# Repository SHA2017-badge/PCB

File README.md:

# PCB
This repository hosts the board files for the SHA2017 badge. There are a couple different revisions:
* _rev0_0_1_: First dev board
* _rev0_0_2_: First dev board with fixed IO error (not produced)
* _rev0_1_0_: "Pre-badge"
* _rev1_0_0_: Semi-final badge design - via under D3 shorts VCC to GND (oops)
* _rev1_0_1_: FINAL Badge design with short fixed and silkscreen art

The badge is designed in Eagle version 6.6.

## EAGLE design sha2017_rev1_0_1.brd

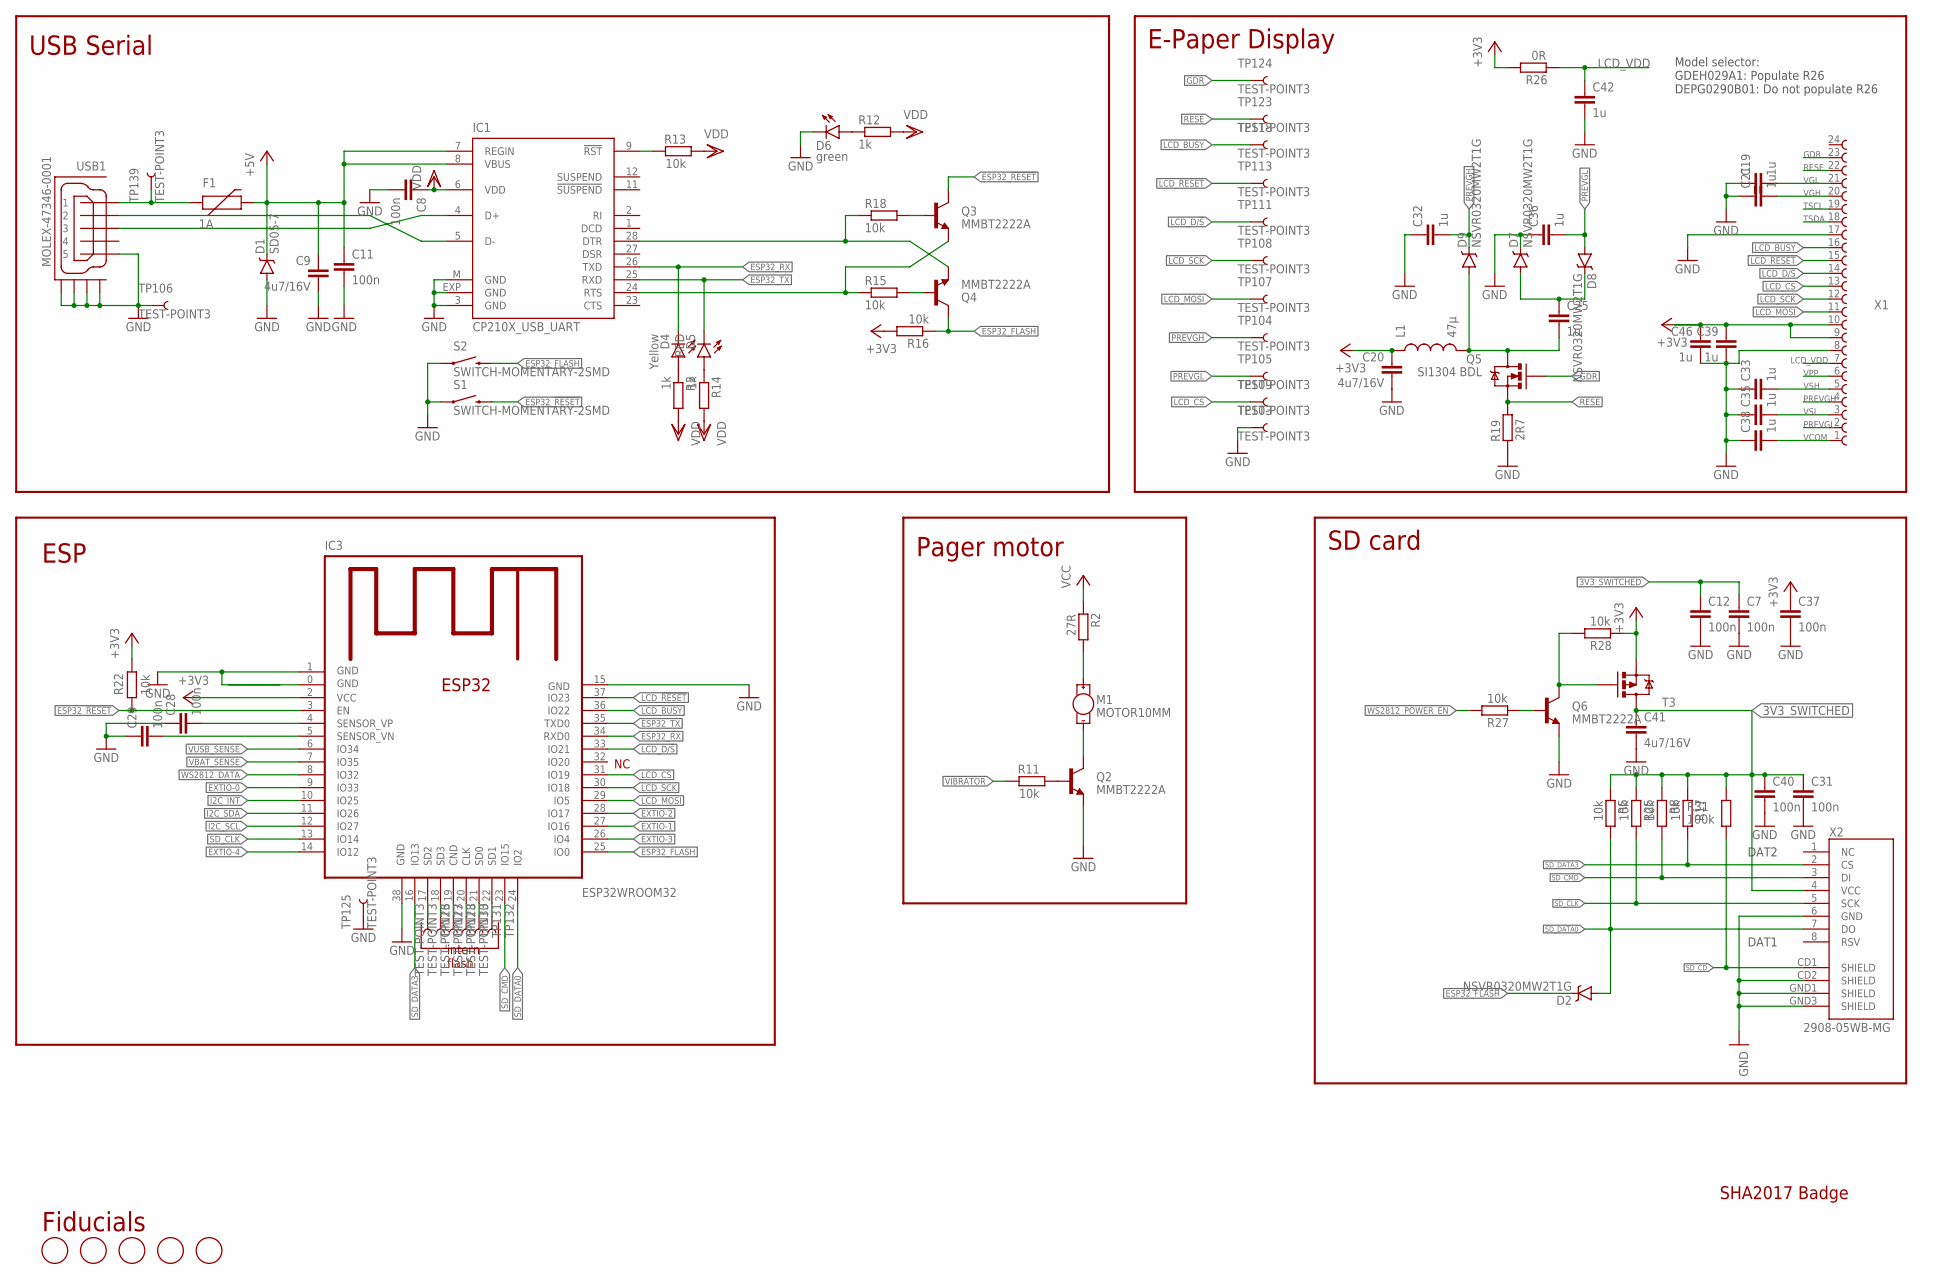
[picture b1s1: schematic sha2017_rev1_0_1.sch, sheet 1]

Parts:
C7, C8, C11, C12, C28, C29, C31, C37, C40: 100n; C0603-DASHES; PARTNO GRM188R71H104KA93D
C9, C20, C41: 4u7/16V; C0805; PARTNO GRM21BR61C475KA88K
C19, C21, C25, C32, C33, C35, C36, C38, C39, C42, C46: 1u; C0603-DASHES; PARTNO GRM188R61E105KA12D
D1: SD05-7; SOD-323; PARTNO SD05-7
D2, D7, D8, D9: NSVR0320MW2T1G; SOD-323; PARTNO BAT20JFILM
D4: Yellow; LED-0603
D5: RED; LED-0603
D6: green; LED-0603
F1: 1A; PTC-1206
FD1, FD2, FD3, FD4, FD5: FIDUCIAL; FIDUCIAL_1MM; PARTNO NAP
IC1: CP210X_USB_UART; MLP28; PARTNO CP2102-GMR
IC3: ESP32WROOM32; ESP32MOD
L1: 47µ; 1210; PARTNO NLCV32T-220K-EF
M1: MOTOR10MM; VIBE-MOTOR-10MM
Q2, Q3, Q4, Q6: MMBT2222A; SOT23-3; PARTNO BC817-25,215
Q5: SI1304 BDL; SOT323; PARTNO SI1308EDL-T1-GE3
R2: 27R; R1206; PARTNO ERJ-3GEYJ220V
R3, R12, R14: 1k; R0603-DASHES; PARTNO ERJ-3GEYJ102V
R5, R8, R11, R13, R15, R16, R17, R18, R22, R25, R27, R28: 10k; R0603-DASHES; PARTNO ERJ-3GEYJ103V
R19: 2R7; R0603-DASHES; PARTNO ERJ-3GEYJ5R1V
R26: 0R; R0603-DASHES; PARTNO ERJ-3GEYJ5R1V
R31: 100k; R0603-DASHES; PARTNO ERJ-3GEYJ104V
S1, S2: SWITCH-MOMENTARY-2SMD; TACTILE-SWITCH-SMD; PARTNO SKQGABE010
T3: MOSFET-PCHANNEL; SOT23-3
TP103, TP104, TP105, TP106, TP107, TP108, TP109, TP111, TP113, TP118, TP123, TP124, TP125, TP126, TP127, TP128, TP130, TP131, TP132, TP139: TEST-POINT3; PAD.03X.03; PARTNO NAP
USB1: MOLEX-47346-0001; MOLEX-47364-0001; PARTNO 10118192-0001LF
X1: 68712414022; PARTNO 68712414022
X2: 2908-05WB-MG; MICRO-SD-SOCKET-PP; PARTNO 2908-05WB-MG

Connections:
3V3_SWITCHED: C7.1, C12.1, C31.1, C40.1, C41.1, R5.2, R8.2, R17.2, R25.2, R31.1, T3.3 (D), X2.4 (VCC); also elsewhere on the board
+3V3: C20.1, C37.1, C39.1, C46.1, IC3.2 (VCC), L1.1, R16.2, R22.1, R26.1, R28.2, T3.2 (S), X1.9, X1.10; also elsewhere on the board
+5V: C9.1, C11.1, D1.C, F1.2, IC1.7 (REGIN), IC1.8 (VBUS); also elsewhere on the board
CD0: IC3.21 (SD0), TP131.P$1
CLK: IC3.20 (CLK), TP130.P$1
CND: IC3.19 (CND), TP128.P$1
ESP32_!RESET: IC3.3 (EN), Q3.3 (C), R22.2, S1.3 (2); also elsewhere on the board
ESP32_FLASH: D2.C, IC3.25 (IO0), Q4.3 (C), R16.1, S2.3 (2); also elsewhere on the board
ESP32_RX: D4.C, IC1.26 (TXD), IC3.34 (RXD0); also elsewhere on the board
ESP32_TX: D5.C, IC1.25 (RXD), IC3.35 (TXD0); also elsewhere on the board
EXTIO-0: IC3.9 (IO33); also elsewhere on the board
EXTIO-1: IC3.27 (IO16); also elsewhere on the board
EXTIO-2: IC3.28 (IO17); also elsewhere on the board
EXTIO-3: IC3.26 (IO4); also elsewhere on the board
EXTIO-4: IC3.14 (IO12); also elsewhere on the board
GDR: Q5.1 (G), TP124.P$1, X1.23
GND: C7.2, C8.2, C9.2, C11.2, C12.2, C19.1, C20.2, C21.1, C28.1, C29.1, C31.2, C32.1, C33.1, C35.1, C36.1, C37.2, C38.1, C39.2, C40.2, C41.2, C42.2, C46.2, D1.A, D6.C, D7.C, IC1.3 (GND), IC1.EXP (GND), IC1.M (GND), IC3.0 (GND), IC3.1 (GND), IC3.15 (GND), IC3.38 (GND), Q2.2 (E), Q6.2 (E), R19.2, S1.1, S2.1, TP103.P$1, TP106.P$1, TP125.P$1, USB1.5, USB1.GND1, USB1.GND2, USB1.GND3, USB1.GND4, X1.8, X1.17, X2.6 (GND), X2.CD2 (SHIELD), X2.GND1 (SHIELD), X2.GND3 (SHIELD); also elsewhere on the board
I2C_INT: IC3.10 (IO25); also elsewhere on the board
I2C_SCL: IC3.12 (IO27); also elsewhere on the board
I2C_SDA: IC3.11 (IO26); also elsewhere on the board
LCD_!RESET: IC3.37 (IO23), TP113.P$1, X1.15
LCD_BUSY: IC3.36 (IO22), TP118.P$1, X1.16
LCD_CS: IC3.31 (IO19), TP109.P$1, X1.13
LCD_D/!S: IC3.33 (IO21), TP111.P$1, X1.14
LCD_MOSI: IC3.29 (IO5), TP107.P$1, X1.11
LCD_SCK: IC3.30 (IO18), TP108.P$1, X1.12
LCD_VDD: C42.1, R26.2, X1.7
unnamed: IC1.9 (!RST), R13.2
unnamed: IC1.24 (RTS), Q3.2 (E), R15.1
unnamed: IC1.28 (DTR), Q4.2 (E), R18.1
unnamed: Q4.1 (B), R15.2
unnamed: Q3.1 (B), R18.2
unnamed: Q6.1 (B), R27.2
unnamed: M1.-, Q2.3 (C)
unnamed: Q6.3 (C), R28.1, T3.1 (G)
unnamed: M1.+, R2.1
unnamed: C25.1, D7.A, D8.C
unnamed: C25.2, D9.A, L1.2, Q5.3 (D)
unnamed: D6.A, R12.1
unnamed: D4.A, R3.1
unnamed: D5.A, R14.1
unnamed: F1.1, TP139.P$1, USB1.1
unnamed: C28.2, IC3.4 (SENSOR_VP)
unnamed: C29.2, IC3.5 (SENSOR_VN)
unnamed: Q2.1 (B), R11.1
PREVGH: C32.2, D9.C, TP104.P$1, X1.4
PREVGL: C36.2, D8.A, TP105.P$1, X1.2
RESE: Q5.2 (S), R19.1, TP123.P$1, X1.22
SD1: IC3.22 (SD1), TP132.P$1
SD2: IC3.17 (SD2), TP126.P$1
SD3: IC3.18 (SD3), TP127.P$1
SD_CD: R31.2, X2.CD1 (SHIELD); also elsewhere on the board
SD_CLK: IC3.13 (IO14), R25.1, X2.5 (SCK)
SD_CMD: IC3.23 (IO15), R8.1, X2.3 (DI)
SD_DATA0: D2.A, IC3.24 (IO2), R5.1, X2.7 (DO)
SD_DATA3: IC3.16 (IO13), R17.1, X2.2 (CS)
TSCL: X1.19
TSDA: X1.18
USB_DN_CON: IC1.5 (D-), USB1.2; also elsewhere on the board
USB_DP_CON: IC1.4 (D+), USB1.3; also elsewhere on the board
VBAT_SENSE: IC3.7 (IO35); also elsewhere on the board
VCC: R2.2; also elsewhere on the board
VCOM: C38.2, X1.1
VDD: C8.1, IC1.6 (VDD), R3.2, R12.2, R13.1, R14.2
VGH: C21.2, X1.20
VGL: C19.2, X1.21
VIBRATOR: R11.2; also elsewhere on the board
VPP: X1.6
VSH: C33.2, X1.5
VSL: C35.2, X1.3
VUSB_SENSE: IC3.6 (IO34); also elsewhere on the board
WS2812_DATA: IC3.8 (IO32); also elsewhere on the board
WS2812_POWER_EN: R27.1; also elsewhere on the board

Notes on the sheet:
USB Serial
E-Paper Display
SD card
intern flash
ESP
Fiducials
Pager motor
DAT1
DAT2
Model selector: GDEH029A1: Populate R26 DEPG0290B01: Do not populate R26
SHA2017 Badge

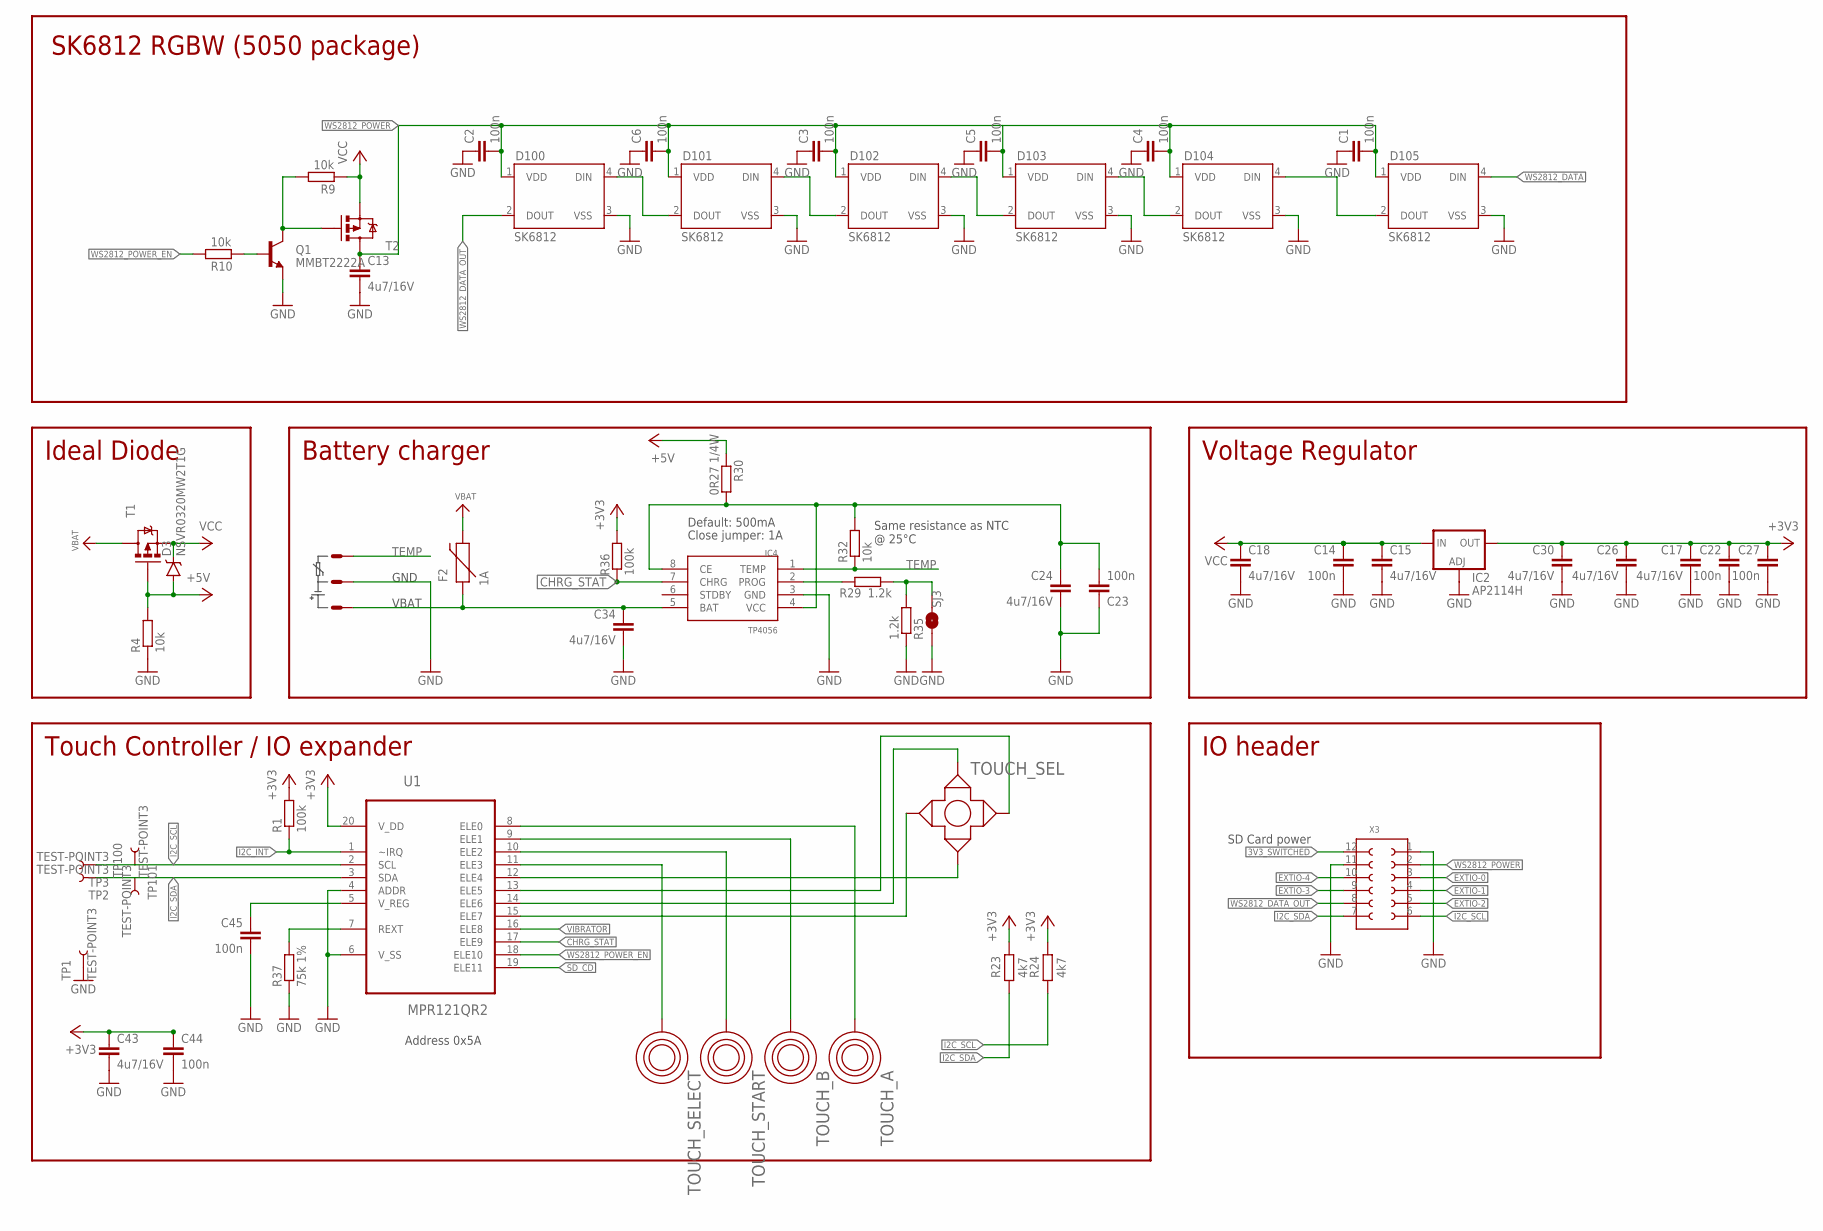
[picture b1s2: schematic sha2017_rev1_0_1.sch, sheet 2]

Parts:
C1, C2, C3, C4, C5, C6, C14, C22, C23, C27, C44, C45: 100n; C0603-DASHES; PARTNO GRM188R71H104KA93D
C13, C15, C17, C18, C24, C26, C30, C34, C43: 4u7/16V; C0805; PARTNO GRM21BR61C475KA88K
D3: NSVR0320MW2T1G; SOD-323; PARTNO BAT20JFILM
D100, D101, D102, D103, D104, D105: SK6812; WS2812B; PARTNO SK6812
F2: 1A; PTC-1206
IC2: AP2114H; SOT223; PARTNO AP7215-33YG-13
IC4: TP4056; SOP-8
Q1: MMBT2222A; SOT23-3; PARTNO BC817-25,215
R1, R36: 100k; R0603-DASHES; PARTNO ERJ-3GEYJ104V
R4, R9, R10: 10k; R0603-DASHES; PARTNO ERJ-3GEYJ103V
R23, R24: 4k7; R0603-DASHES; PARTNO ERJ-3GEYJ103V
R29, R35: 1.2k; R0603-DASHES; PARTNO ERJ-3GEYJ222V
R30: 0R27 1/4W; R1206; PARTNO ERJ-3GEYJ154V
R32: 10k; R0603-DASHES; PARTNO ERJ-3GEYJ154V
R37: 75k 1%; R0603-DASHES; PARTNO ERJ-3GEYJ104V
SJ3: JUMPER-PAD-2-NOYES_SILK; PAD-JUMPER-2-NO_YES_SILK; PARTNO NAP
T1, T2: MOSFET-PCHANNEL; SOT23-3
TOUCH_A: TOUCHROUND; TOUCH_BUTTON; PARTNO NAP
TOUCH_B: TOUCHROUND; TOUCH_BUTTON; PARTNO NAP
TOUCH_SEL: TOUCH_CROSS; PARTNO NAP
TOUCH_SELECT: TOUCHSELECT; TOUCH_SELECT
TOUCH_START: TOUCHSELECT; TOUCH_SELECT
TP1, TP2, TP3, TP100, TP101: TEST-POINT3; PAD.03X.03; PARTNO NAP
U1: MPR121QR2; QFN40P300X300X60-20N
X3: 610X12243021; PARTNO 517-153208-2020-TB
X4: JST-PH3

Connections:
3V3_SWITCHED: X3.12 (1); also elsewhere on the board
+3V3: C17.1, C22.1, C26.1, C27.1, C30.1, C43.1, C44.1, IC2.4 (OUT), R1.2, R23.1, R24.1, R36.2, U1.20 (V_DD); also elsewhere on the board
+5V: D3.A, R4.2, R30.1, T1.1 (G); also elsewhere on the board
CHRG_STAT: IC4.7 (CHRG), R36.1, U1.17 (ELE9)
EXTIO-0: X3.3 (10); also elsewhere on the board
EXTIO-1: X3.4 (9); also elsewhere on the board
EXTIO-2: X3.5 (8); also elsewhere on the board
EXTIO-3: X3.9 (4); also elsewhere on the board
EXTIO-4: X3.10 (3); also elsewhere on the board
GND: C1.1, C2.1, C3.1, C4.1, C5.1, C6.1, C13.2, C14.2, C15.2, C17.2, C18.2, C22.2, C23.1, C24.2, C26.2, C27.2, C30.2, C34.2, C43.2, C44.2, C45.2, D100.3 (VSS), D101.3 (VSS), D102.3 (VSS), D103.3 (VSS), D104.3 (VSS), D105.3 (VSS), IC2.1 (ADJ), IC4.3 (GND), Q1.2 (E), R4.1, R35.2, R37.1, SJ3.1, TP1.P$1, U1.4 (ADDR), U1.6 (V_SS), X3.1 (12), X3.11 (2), X4.2; also elsewhere on the board
I2C_INT: R1.1, U1.1 (~IRQ); also elsewhere on the board
I2C_SCL: R24.2, TP3.P$1, TP100.P$1, U1.2 (SCL), X3.6 (7); also elsewhere on the board
I2C_SDA: R23.2, TP2.P$1, TP101.P$1, U1.3 (SDA), X3.7 (6); also elsewhere on the board
unnamed: TOUCH_B.P$1, U1.9 (ELE1)
unnamed: D100.4 (DIN), D101.2 (DOUT)
unnamed: D103.4 (DIN), D104.2 (DOUT)
unnamed: D104.4 (DIN), D105.2 (DOUT)
unnamed: TOUCH_A.P$1, U1.8 (ELE0)
unnamed: IC4.2 (PROG), R29.1
unnamed: R29.2, R35.1, SJ3.2
unnamed: C23.2, C24.1, IC4.4 (VCC), IC4.8 (CE), R30.2, R32.2
unnamed: D101.4 (DIN), D102.2 (DOUT)
unnamed: C45.1, U1.5 (V_REG)
unnamed: R37.2, U1.7 (REXT)
unnamed: TOUCH_START.P$1, U1.10 (ELE2)
unnamed: TOUCH_SELECT.P$1, U1.11 (ELE3)
unnamed: TOUCH_SEL.D (DOWN), U1.12 (ELE4)
unnamed: TOUCH_SEL.L (LEFT), U1.15 (ELE7)
unnamed: TOUCH_SEL.UP, U1.14 (ELE6)
unnamed: TOUCH_SEL.R (RIGHT), U1.13 (ELE5)
unnamed: C34.1, F2.1, IC4.5 (BAT), X4.3
unnamed: D102.4 (DIN), D103.2 (DOUT)
unnamed: Q1.1 (B), R10.2
unnamed: Q1.3 (C), R9.1, T2.1 (G)
SD_CD: U1.19 (ELE11); also elsewhere on the board
TEMP: IC4.1 (TEMP), R32.1, X4.1
VBAT: F2.2, T1.3 (D); also elsewhere on the board
VCC: C14.1, C15.1, C18.1, D3.C, IC2.3 (IN), R9.2, T1.2 (S), T2.2 (S); also elsewhere on the board
VIBRATOR: U1.16 (ELE8); also elsewhere on the board
WS2812_DATA: D105.4 (DIN); also elsewhere on the board
WS2812_DATA_OUT: D100.2 (DOUT), X3.8 (5)
WS2812_POWER: C1.2, C2.2, C3.2, C4.2, C5.2, C6.2, C13.1, D100.1 (VDD), D101.1 (VDD), D102.1 (VDD), D103.1 (VDD), D104.1 (VDD), D105.1 (VDD), T2.3 (D), X3.2 (11); also elsewhere on the board
WS2812_POWER_EN: R10.1, U1.18 (ELE10); also elsewhere on the board

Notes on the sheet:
Voltage Regulator
Battery charger
Ideal Diode
Default: 500mA
Close jumper: 1A
GND
VBAT
Same resistance as NTC @ 25°C
SK6812 RGBW (5050 package)
Touch Controller / IO expander
Address 0x5A
IO header
SD Card power

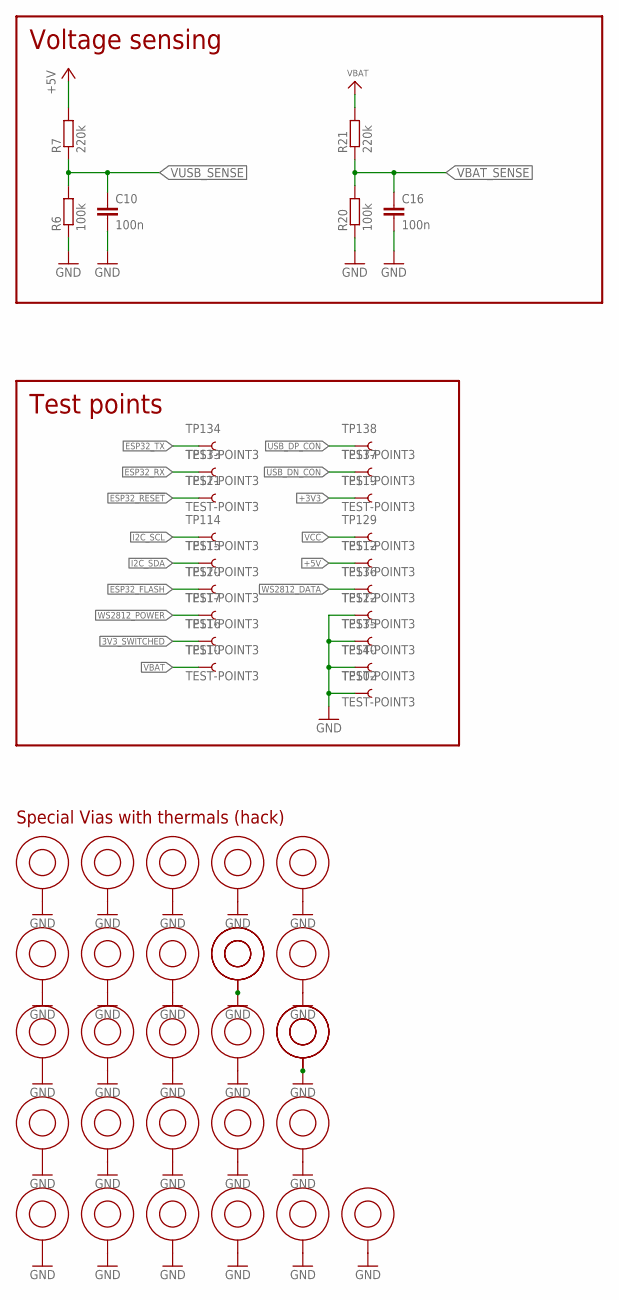
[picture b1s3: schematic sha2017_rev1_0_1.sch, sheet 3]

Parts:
$$U$1, $$U$2, $$U$3, $$U$4, $$U$5, $$U$6, $$U$7, $$U$8, $$U$9: VIA; PARTNO NAP
C10, C16: 100n; C0603-DASHES; PARTNO GRM188R71H104KA93D
R6, R20: 100k; R0603-DASHES; PARTNO ERJ-3GEYJ104V
R7, R21: 220k; R0603-DASHES; PARTNO ERJ-3GEYJ224V
TP102, TP110, TP112, TP114, TP115, TP116, TP117, TP119, TP120, TP121, TP122, TP129, TP133, TP134, TP135, TP136, TP137, TP138, TP140: TEST-POINT3; PAD.03X.03; PARTNO NAP
U$2, U$3, U$4, U$5, U$6, U$10, U$11, U$12, U$13, U$14, U$15, U$16, U$17, U$18, U$19, U$20, U$21, U$22, U$23: VIA; PARTNO NAP

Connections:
3V3_SWITCHED: TP116.P$1; also elsewhere on the board
+3V3: TP119.P$1; also elsewhere on the board
+5V: R7.2, TP112.P$1; also elsewhere on the board
ESP32_!RESET: TP121.P$1; also elsewhere on the board
ESP32_FLASH: TP120.P$1; also elsewhere on the board
ESP32_RX: TP133.P$1; also elsewhere on the board
ESP32_TX: TP134.P$1; also elsewhere on the board
GND: $$U$1.P$1, $$U$2.P$1, $$U$3.P$1, $$U$4.P$1, $$U$5.P$1, $$U$6.P$1, $$U$7.P$1, $$U$8.P$1, $$U$9.P$1, C10.2, C16.2, R6.1, R20.1, TP102.P$1, TP122.P$1, TP135.P$1, TP140.P$1, U$2.P$1, U$3.P$1, U$4.P$1, U$5.P$1, U$6.P$1, U$10.P$1, U$11.P$1, U$12.P$1, U$13.P$1, U$14.P$1, U$15.P$1, U$16.P$1, U$17.P$1, U$18.P$1, U$19.P$1, U$20.P$1, U$21.P$1, U$22.P$1, U$23.P$1; also elsewhere on the board
I2C_SCL: TP114.P$1; also elsewhere on the board
I2C_SDA: TP115.P$1; also elsewhere on the board
USB_DN_CON: TP137.P$1; also elsewhere on the board
USB_DP_CON: TP138.P$1; also elsewhere on the board
VBAT: R21.2, TP110.P$1; also elsewhere on the board
VBAT_SENSE: C16.1, R20.2, R21.1; also elsewhere on the board
VCC: TP129.P$1; also elsewhere on the board
VUSB_SENSE: C10.1, R6.2, R7.1; also elsewhere on the board
WS2812_DATA: TP136.P$1; also elsewhere on the board
WS2812_POWER: TP117.P$1; also elsewhere on the board

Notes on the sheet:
Special Vias with thermals (hack)
Test points
Voltage sensing

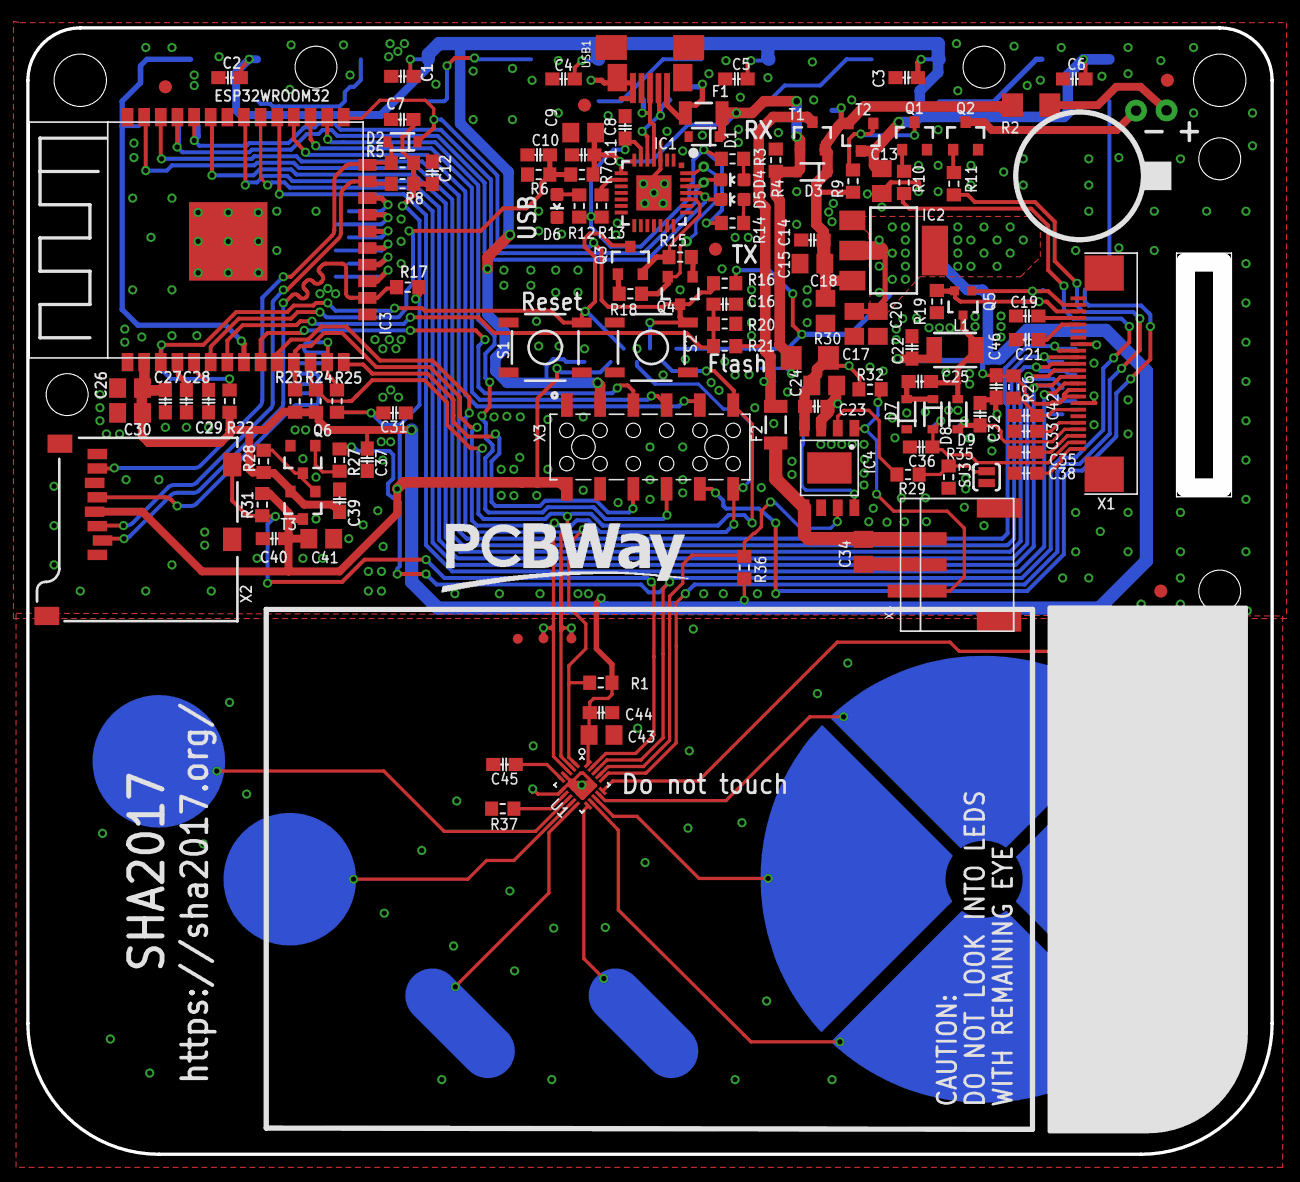
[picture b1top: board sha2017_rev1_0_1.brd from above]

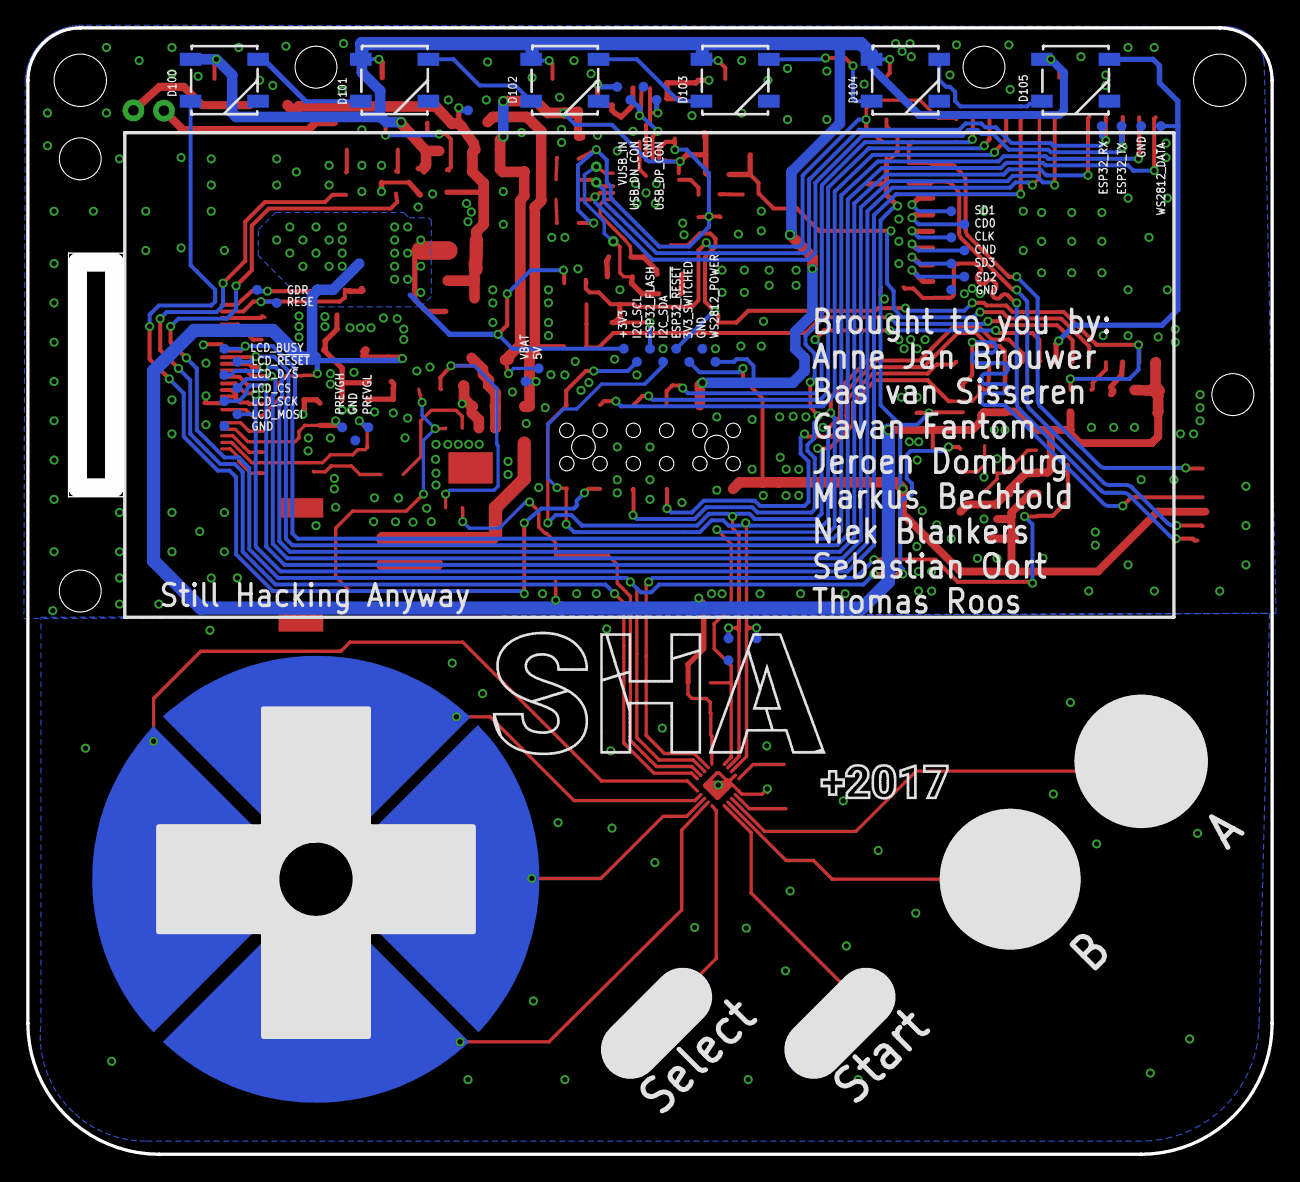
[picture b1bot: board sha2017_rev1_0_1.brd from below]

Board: 2 copper layers, 95.0 x 86.0 mm, 204 parts (52 on the bottom side), 96 nets.

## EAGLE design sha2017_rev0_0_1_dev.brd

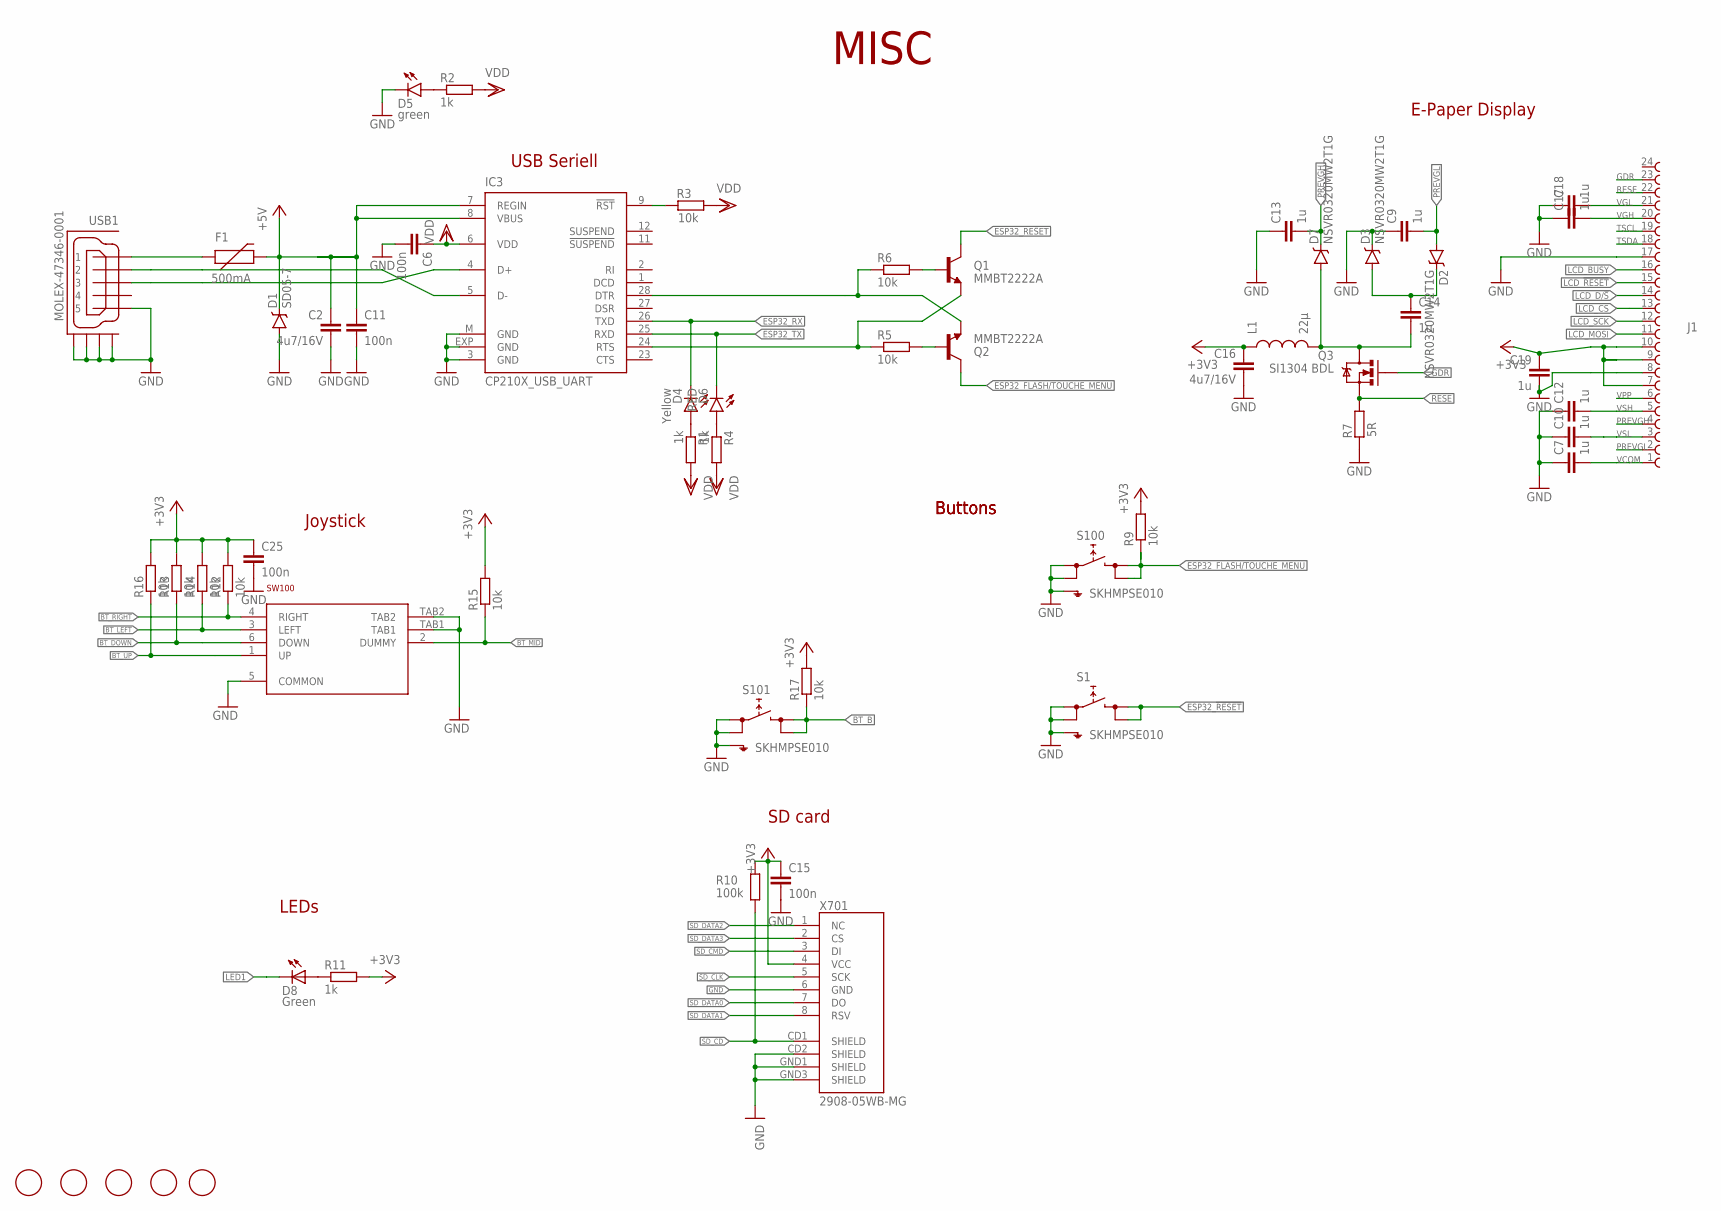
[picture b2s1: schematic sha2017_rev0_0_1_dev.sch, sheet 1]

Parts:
C2, C16: 4u7/16V; C0805; PARTNO GRM21BR61C475KA88K
C6, C11, C15, C25: 100n; C0603; PARTNO GRM188R71H104KA93D
C7, C9, C10, C12, C13, C14, C17, C18, C19: 1u; C0603; PARTNO GRM188R61E105KA12D
D1: SD05-7; SOD-323; PARTNO PMEG4005EJ,115
D2, D3, D7: NSVR0320MW2T1G; SOD-323; PARTNO BAT20JFILM
D4: Yellow; LED-0603
D5: green; LED-0603
D6: RED; LED-0603
D8: Green; SML1206; PARTNO 156120VS75300
F1: 500mA; PTC-1206; PARTNO 0ZCJ0025FF2E
FD1, FD2, FD3, FD4, FD5: FIDUCIAL; FIDUCIAL_1MM
IC3: CP210X_USB_UART; MLP28; PARTNO CP2102-GMR
J1: 68712414022; PARTNO 68712414022
L1: 22µ; 1210; PARTNO NLCV32T-220K-EF
Q1, Q2: MMBT2222A; SOT23-3; PARTNO BC817-25,215
Q3: SI1304 BDL; SOT323; PARTNO SI1308EDL-T1-GE3
R1, R2, R4, R11: 1k; R0603; PARTNO ERJ-3GEYJ102V
R3, R5, R6, R9, R12, R13, R14, R15, R16, R17: 10k; R0603; PARTNO ERJ-3GEYJ103V
R7: 5R; R0603-DASHES; PARTNO ERJ-3GEYJ5R1V
R10: 100k; R0603; PARTNO CRCW0603100KFKEA
S1, S100, S101: SKHMPSE010; SKHMPXE010; PARTNO SKHMQME010
SW100: MCMT5-F-V; PARTNO SKRHAAE010
USB1: MOLEX-47346-0001; MOLEX-47364-0001; PARTNO 10118194-0001LF
X701: 2908-05WB-MG; MICRO-SD-SOCKET-PP; PARTNO 2908-05WB-MG

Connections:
+3V3: C15.1, C16.1, C19.1, C25.1, J1.7, J1.9, J1.10, L1.1, R9.2, R10.1, R11.2, R12.2, R13.2, R14.2, R15.2, R16.2, R17.2, X701.4 (VCC); also elsewhere on the board
+5V: C2.1, C11.1, D1.C, F1.2, IC3.7 (REGIN), IC3.8 (VBUS); also elsewhere on the board
BT_B: R17.1, S101.3 (2.1), S101.4 (2.2); also elsewhere on the board
BT_DOWN: R13.1, SW100.6 (DOWN); also elsewhere on the board
BT_LEFT: R14.1, SW100.3 (LEFT); also elsewhere on the board
BT_MID: R15.1, SW100.2 (DUMMY); also elsewhere on the board
BT_RIGHT: R12.1, SW100.4 (RIGHT); also elsewhere on the board
BT_UP: R16.1, SW100.1 (UP); also elsewhere on the board
ESP32_!RESET: Q1.3 (C), S1.3 (2.1), S1.4 (2.2); also elsewhere on the board
ESP32_FLASH/TOUCHE_MENU: Q2.3 (C), R9.1, S100.3 (2.1), S100.4 (2.2); also elsewhere on the board
ESP32_RX: D4.C, IC3.26 (TXD); also elsewhere on the board
ESP32_TX: D6.C, IC3.25 (RXD); also elsewhere on the board
GDR: J1.23, Q3.1 (G)
GND: C2.2, C6.2, C7.1, C9.1, C10.1, C11.2, C12.1, C13.1, C15.2, C16.2, C17.1, C18.1, C19.2, C25.2, D1.A, D3.C, D5.C, IC3.3 (GND), IC3.EXP (GND), IC3.M (GND), J1.8, J1.17, R7.2, S1.1 (1.1), S1.2 (1.2), S1.5 (SH), S100.1 (1.1), S100.2 (1.2), S100.5 (SH), S101.1 (1.1), S101.2 (1.2), S101.5 (SH), SW100.5 (COMMON), SW100.TAB1, SW100.TAB2, USB1.5, USB1.GND1, USB1.GND2, USB1.GND3, USB1.GND4, X701.6 (GND), X701.CD2 (SHIELD), X701.GND1 (SHIELD), X701.GND3 (SHIELD); also elsewhere on the board
LCD_!RESET: J1.15; also elsewhere on the board
LCD_BUSY: J1.16; also elsewhere on the board
LCD_CS: J1.13; also elsewhere on the board
LCD_D/!S: J1.14; also elsewhere on the board
LCD_MOSI: J1.11; also elsewhere on the board
LCD_SCK: J1.12; also elsewhere on the board
LED1: D8.C; also elsewhere on the board
unnamed: IC3.9 (!RST), R3.2
unnamed: IC3.24 (RTS), Q1.2 (E), R5.1
unnamed: IC3.28 (DTR), Q2.2 (E), R6.1
unnamed: Q2.1 (B), R5.2
unnamed: Q1.1 (B), R6.2
unnamed: C14.1, D2.C, D3.A
unnamed: C14.2, D7.A, L1.2, Q3.3 (D)
unnamed: D8.A, R11.1
unnamed: D5.A, R2.1
unnamed: D4.A, R1.1
unnamed: D6.A, R4.1
unnamed: F1.1, USB1.1
PREVGH: C13.2, D7.C, J1.4
PREVGL: C9.2, D2.A, J1.2
RESE: J1.22, Q3.2 (S), R7.1
SD_CD: R10.2, X701.CD1 (SHIELD); also elsewhere on the board
SD_CLK: X701.5 (SCK); also elsewhere on the board
SD_CMD: X701.3 (DI); also elsewhere on the board
SD_DATA0: X701.7 (DO); also elsewhere on the board
SD_DATA1: X701.8 (RSV); also elsewhere on the board
SD_DATA2: X701.1 (NC); also elsewhere on the board
SD_DATA3: X701.2 (CS); also elsewhere on the board
TSCL: J1.19
TSDA: J1.18
USB_DN_CON: IC3.5 (D-), USB1.2
USB_DP_CON: IC3.4 (D+), USB1.3
VCOM: C7.2, J1.1
VDD: C6.1, IC3.6 (VDD), R1.2, R2.2, R3.1, R4.2
VGH: C17.2, J1.20
VGL: C18.2, J1.21
VPP: J1.6
VSH: C12.2, J1.5
VSL: C10.2, J1.3

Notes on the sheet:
MISC
USB Seriell
E-Paper Display
Joystick
Buttons
LEDs
SD card

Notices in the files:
parts and their libraries:
SparkFun-DigitalIC: Licensing: Creative Commons ShareAlike 4.0 International - https://creativecommons.org/licenses/by-sa/4.0
EAGLE-FPC_CONNECTOR_AND_FFC_CAB-rev1: Copyright: Würth Elektronik
